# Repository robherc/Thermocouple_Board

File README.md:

# Thermocouple_Board
Ultra-fast, Ultra-Precise Thermocouple reading board with SPI and Analog outputs

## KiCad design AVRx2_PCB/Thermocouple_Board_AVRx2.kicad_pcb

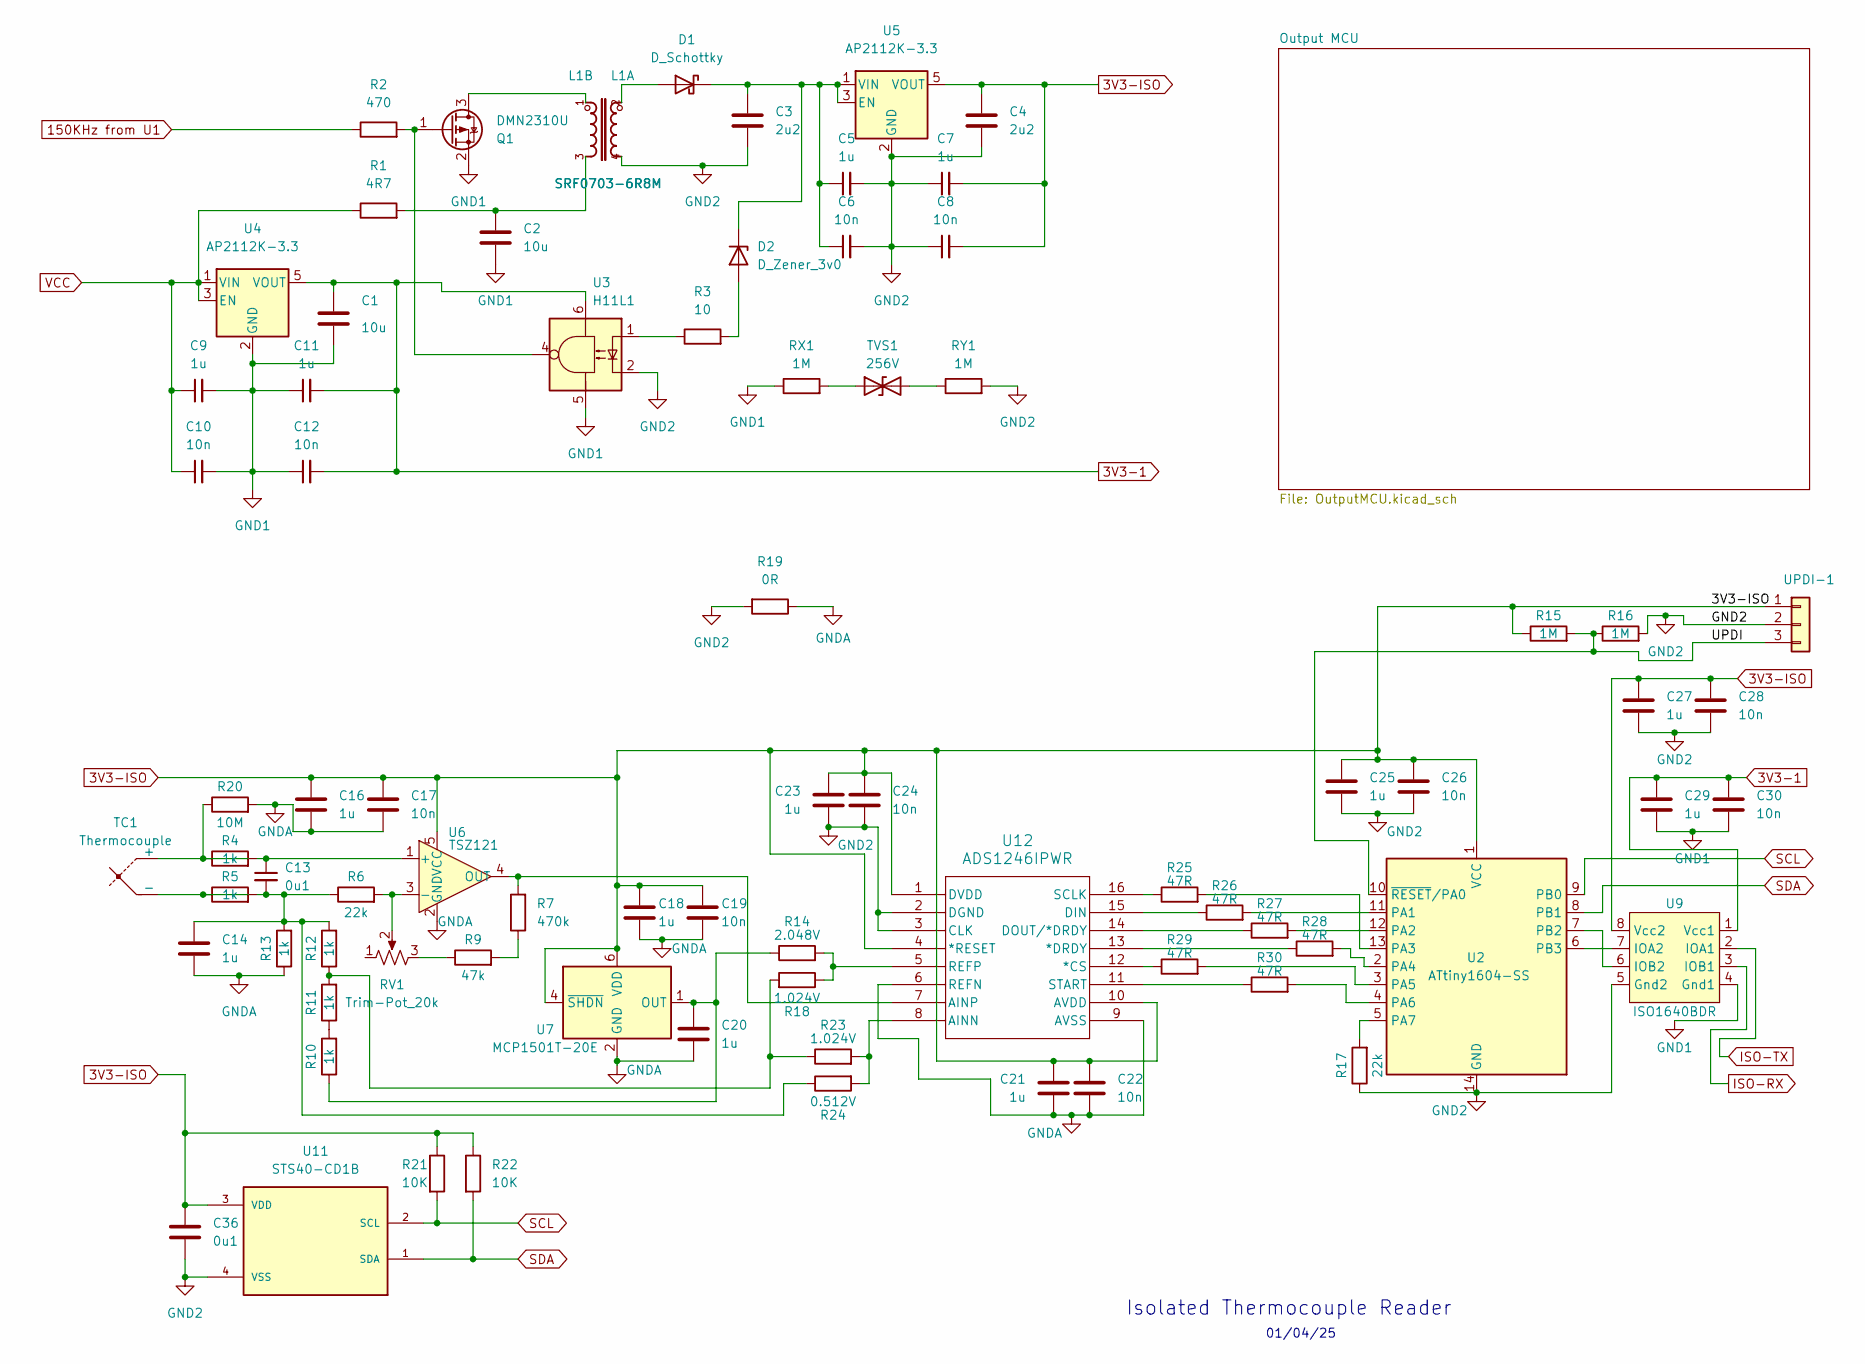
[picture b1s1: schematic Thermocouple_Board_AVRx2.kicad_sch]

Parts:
C1, C2: 10u; C_0805_2012Metric_Pad1.18x1.45mm_HandSolder
C3, C4: 2u2; C_0603_1608Metric
C5, C7, C9, C11, C14, C16, C18, C20, C21, C23, C25, C27, C29: 1u; C_0402_1005Metric
C6, C8, C10, C12, C17, C19, C22, C24, C26, C28, C30: 10n; C_0402_1005Metric
C13, C36: 0u1; C_0402_1005Metric
D1: D_Schottky; D_2010_5025Metric_Pad1.52x2.65mm_HandSolder
D2: D_Zener_3v0; D_SOD-123
J6: UPDI-1; PinHeader_1x03_P2.54mm_Vertical
L1: SRF0703-6R8M; 0703; MPN SRF0703-220M
Q1: DMN2310U; SOT-23
R1: 4R7; R_2512_6332Metric
R2: 470; R_0402_1005Metric
R3: 10; R_1206_3216Metric
R4, R5, R10, R11, R12, R13: 1k; R_0603_1608Metric
R6, R17: 22k; R_0603_1608Metric
R7: 470k; R_0603_1608Metric
R9: 47k; R_0603_1608Metric
R14: 2.048V; R_0402_1005Metric_Pad0.72x0.64mm_HandSolder
R15, R16: 1M; R_0603_1608Metric
R18, R23: 1.024V; R_0402_1005Metric_Pad0.72x0.64mm_HandSolder
R19: 0R; R_1206_3216Metric_Pad1.30x1.75mm_HandSolder
R20: 10M; R_0402_1005Metric
R21, R22: 10K; R_0603_1608Metric
R24: 0.512V; R_0402_1005Metric_Pad0.72x0.64mm_HandSolder
R25, R26, R27, R28, R29, R30: 47R; R_0603_1608Metric
RV1: Trim-Pot_20k; TRIM_TC33X-2-203E
RX1: 1M; R_0603_1608Metric
RY1: 1M; R_0603_1608Metric
TC1: Thermocouple; TypeKSocket
TVS1: 256V; DO-214AA
U2: ATtiny1604-SS; SOIC-14_3.9x8.7mm_P1.27mm
U3: H11L1; H11L1-4
U4, U5: AP2112K-3.3; SOT-23-5
U6: TSZ121; SOT-353_SC-70-5
U7: MCP1501T-20E; SOT-23-6
U9: ISO1640BDR; SOIC-8_3.9x4.9mm_P1.27mm
U11: STS40-CD1B; STS4X
U12: ADS1246IPWR; PW16

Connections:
3V3-1: C1.1, C11.2, C12.2, C29.1, C30.1, U3.6, U4.5 (VOUT), U9.1 (Vcc1); also elsewhere on the board
3V3-ISO: C4.1, C7.2, C8.2, C16.1, C17.1, C18.1, C19.1, C21.1, C22.1, C23.1, C24.1, C25.1, C26.1, C27.1, C28.1, C36.1, J6.1, R15.1, R21.1, R22.1, U2.1 (VCC), U5.5 (VOUT), U6.5 (VCC), U7.4 (~SHDN), U7.6 (VDD), U9.8 (Vcc2), U11.3 (VDD), U12.1 (DVDD), U12.4 (*RESET), U12.10 (AVDD)
150KHz from U1: R2.1; also elsewhere on the board
/UPDI: J6.3, R15.2, R16.1, U2.10 (~RESET/PA0)
GND1: C1.2, C2.2, C9.2, C10.2, C11.1, C12.1, C29.2, C30.2, Q1.2 (S), RX1.1, U3.5, U4.2 (GND), U4.4 (NC), U9.4 (Gnd1); also elsewhere on the board
GND2: C3.2, C4.2, C5.2, C6.2, C7.1, C8.1, C23.2, C24.2, C25.2, C26.2, C27.2, C28.2, C36.2, J6.2, L1.4, R16.2, R17.1, R19.2, RY1.2, U2.14 (GND), U3.2, U3.3, U5.2 (GND), U5.4 (NC), U9.5 (Gnd2), U11.4 (VSS), U12.2 (DGND), U12.3 (CLK)
GNDA: C14.2, C16.2, C17.2, C18.2, C19.2, C20.2, C21.2, C22.2, R13.1, R19.1, R20.2, U6.2 (GND), U7.2 (GND), U7.3 (GND), U7.5 (GND), U12.6 (REFN), U12.9 (AVSS)
ISO-RX: U9.3 (IOB1); also elsewhere on the board
ISO-TX: U9.2 (IOA1); also elsewhere on the board
unnamed: C2.1, L1.3, R1.2
unnamed: C13.2, C14.1, R5.2, R6.1, R12.2, R13.2, R24.1
unnamed: D1.2 (A), L1.2
unnamed: C3.1, C5.1, C6.1, D1.1 (K), D2.1 (K), U5.1 (VIN), U5.3 (EN)
unnamed: D2.2 (A), R3.2
unnamed: L1.1, Q1.3 (D)
unnamed: Q1.1 (G), R2.2, U3.4
unnamed: R3.1, U3.1
unnamed: R7.1, R9.2
unnamed: R9.1, RV1.3
unnamed: R10.2, R11.1
unnamed: R11.2, R12.1, R18.2, R23.1
unnamed: R4.1, R20.1, TC1.1 (+)
unnamed: R5.1, TC1.2 (-)
unnamed: RX1.2, TVS1.1 (A1)
unnamed: RY1.1, TVS1.2 (A2)
unnamed: R26.2, U2.11 (PA1)
unnamed: R27.2, U2.12 (PA2)
unnamed: R25.2, U2.13 (PA3)
unnamed: R28.2, U2.2 (PA4)
unnamed: R29.2, U2.3 (PA5)
unnamed: R30.2, U2.4 (PA6)
unnamed: R17.2, U2.5 (PA7)
unnamed: U2.7 (PB2), U9.6 (IOB2)
unnamed: U2.6 (PB3), U9.7 (IOA2)
unnamed: C13.1, R4.2, U6.1 (+)
unnamed: R6.2, RV1.2, U6.3 (-)
unnamed: C20.1, R10.1, R14.1, U7.1 (OUT)
unnamed: R29.1, U12.12 (*CS)
unnamed: R28.1, U12.13 (*DRDY)
unnamed: R23.2, R24.2, U12.8 (AINN)
unnamed: R7.2, U6.4 (OUT), U12.7 (AINP)
unnamed: R26.1, U12.15 (DIN)
unnamed: R27.1, U12.14 (DOUT/*DRDY)
unnamed: R14.2, R18.1, U12.5 (REFP)
unnamed: R25.1, U12.16 (SCLK)
unnamed: R30.1, U12.11 (START)
SCL: R21.2, U2.9 (PB0), U11.2 (SCL)
SDA: R22.2, U2.8 (PB1), U11.1 (SDA)
VCC: C9.1, C10.1, R1.1, U4.1 (VIN), U4.3 (EN); also elsewhere on the board

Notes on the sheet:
Isolated Thermocouple Reader
01/04/25

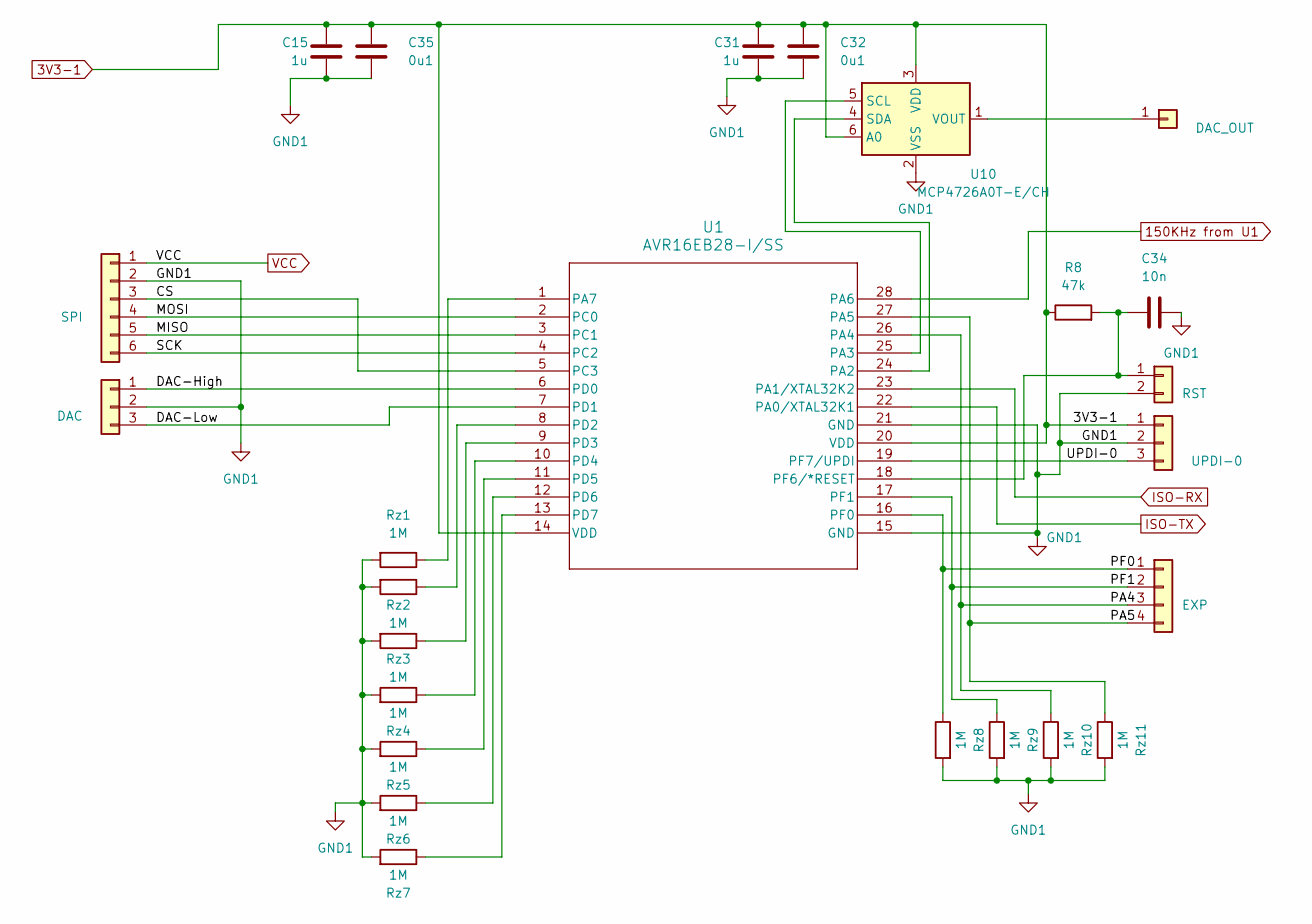
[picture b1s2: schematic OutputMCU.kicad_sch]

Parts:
C15, C31: 1u; C_0402_1005Metric
C32, C35: 0u1; C_0402_1005Metric
C34: 10n; C_0402_1005Metric
J1: DAC_OUT; PinHeader_1x01_P2.54mm_Vertical
J2: SPI; PinHeader_1x06_P2.54mm_Vertical
J3: RST; PinHeader_1x02_P2.54mm_Vertical
J4: DAC; PinHeader_1x03_P2.54mm_Vertical
J5: UPDI-0; PinHeader_1x03_P2.54mm_Vertical
J7: EXP; PinHeader_1x04_P2.54mm_Vertical
R8: 47k; R_0603_1608Metric
Rz1, Rz2, Rz3, Rz4, Rz5, Rz6, Rz7, Rz8, Rz9, Rz10, Rz11: 1M; R_0603_1608Metric
U1: AVR16EB28-I/SS; SSOP28_SS_MCH
U10: MCP4726A0T-E/CH; SOT-23-6

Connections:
3V3-1: C15.1, C31.1, C32.1, C35.1, J5.1, R8.1, U1.14 (VDD), U1.20 (VDD), U10.3 (VDD), U10.6 (A0); also elsewhere on the board
150KHz from U1: U1.28 (PA6); also elsewhere on the board
/Output MCU/CS: J2.3, U1.5 (PC3)
/Output MCU/DAC-High: J4.1, U1.6 (PD0)
/Output MCU/DAC-Low: J4.3, U1.7 (PD1)
/Output MCU/MISO: J2.5, U1.3 (PC1)
/Output MCU/MOSI: J2.4, U1.2 (PC0)
/Output MCU/PA4: J7.3, Rz10.1, U1.26 (PA4)
/Output MCU/PA5: J7.4, Rz11.1, U1.27 (PA5)
/Output MCU/PF0: J7.1, Rz8.1, U1.16 (PF0)
/Output MCU/PF1: J7.2, Rz9.1, U1.17 (PF1)
/Output MCU/SCK: J2.6, U1.4 (PC2)
/Output MCU/UPDI-0: J5.3, U1.19 (PF7/UPDI)
GND1: C15.2, C31.2, C32.2, C34.1, C35.2, J2.2, J3.2, J4.2, J5.2, Rz1.2, Rz2.2, Rz3.2, Rz4.2, Rz5.2, Rz6.2, Rz7.2, Rz8.2, Rz9.2, Rz10.2, Rz11.2, U1.15 (GND), U1.21 (GND), U10.2 (VSS); also elsewhere on the board
ISO-RX: U1.23 (PA1/XTAL32K2); also elsewhere on the board
ISO-TX: U1.22 (PA0/XTAL32K1); also elsewhere on the board
unnamed: J1.1, U10.1 (VOUT)
unnamed: C34.2, J3.1, R8.2, U1.18 (PF6/*RESET)
unnamed: U1.24 (PA2), U10.4 (SDA)
unnamed: U1.25 (PA3), U10.5 (SCL)
unnamed: Rz1.1, U1.1 (PA7)
unnamed: Rz2.1, U1.8 (PD2)
unnamed: Rz3.1, U1.9 (PD3)
unnamed: Rz4.1, U1.10 (PD4)
unnamed: Rz5.1, U1.11 (PD5)
unnamed: Rz6.1, U1.12 (PD6)
unnamed: Rz7.1, U1.13 (PD7)
VCC: J2.1; also elsewhere on the board

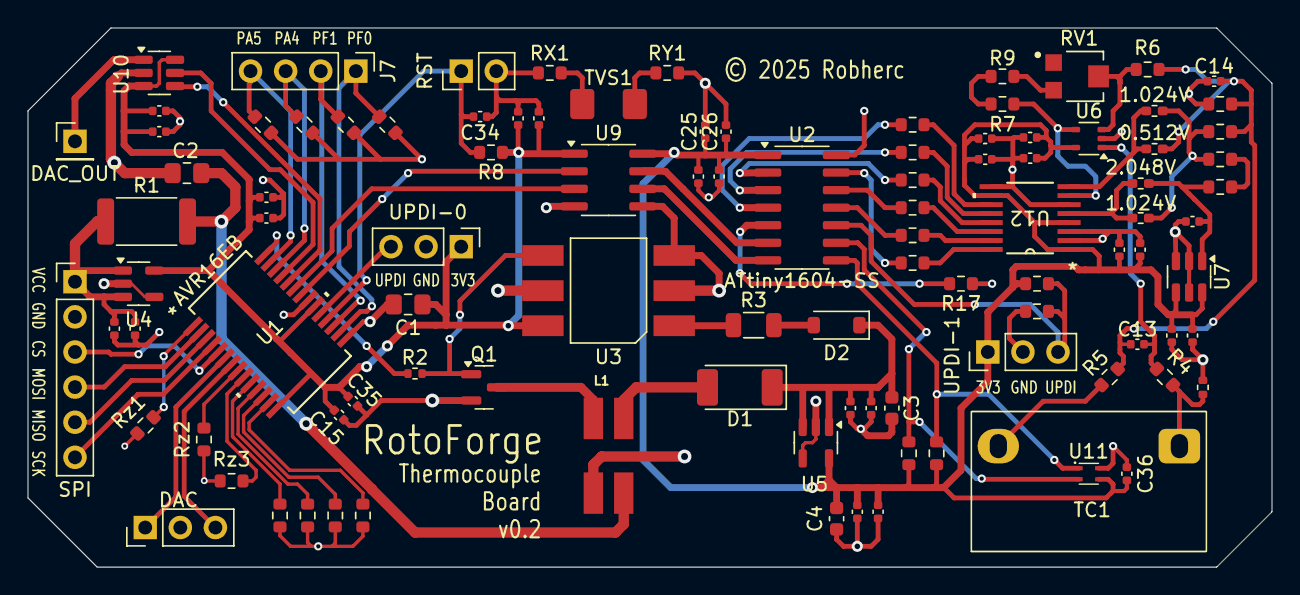
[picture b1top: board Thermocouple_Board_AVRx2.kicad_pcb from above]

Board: 2 copper layers, 90.0 x 39.0 mm, 103 parts (1 on the bottom side), 71 nets.

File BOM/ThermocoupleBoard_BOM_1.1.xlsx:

Source: | /home/robherc/Projects/RotoForge/Isolated Thermocouple Board/ThermocoupleBoard1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
Date: | Fri 17 Jan 2025 01:48:11 AM EST
Tool: | Eeschema 7.0.11+dfsg-1build4
Generator: | /usr/share/kicad/plugins/bom_csv_grouped_by_value_with_fp.py
Component Count: | 85
Ref | Qnty | Value | Cmp name | Footprint | Description | Part # | Vendor | Link
C1, C2 | 2 | 10u | C | Capacitor_SMD:C_0805_2012Metric | Ceramic capacitor | 1276-1096-1-ND | DigiKey | https://www.digikey.com/en/products/detail/samsung-electro-m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
C3, C4 | 2 | 2u2 | C | Capacitor_SMD:C_0603_1608Metric | Ceramic capacitor | 1276-1040-1-ND | DigiKey | https://www.digikey.com/en/products/detail/samsung-electro-m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
C5, C7, C9, C11, C14, C15, C16, C18, C20, C21, C23, C25, C27, C29 | 14 | 1u | C | Capacitor_SMD:C_0402_1005Metric | Ceramic capacitor | 1276-1076-1-ND | DigiKey | https://www.digikey.com/en/products/detail/samsung-electro-m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
C6, C8, C10, C12, C17, C19, C22, C24, C26, C28, C30, C34 | 12 | 10n | C | Capacitor_SMD:C_0402_1005Metric | Ceramic capacitor | 490-1313-1-ND | DigiKey | https://www.digikey.com/en/products/detail/murata-electronic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
C13, C35, C36 | 3 | 0u1 | C | Capacitor_SMD:C_0402_1005Metric | Ceramic capacitor | 490-6328-1-ND | DigiKey | https://www.digikey.com/en/products/detail/murata-electronic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
C33 | 1 | 0.47u | C | Capacitor_SMD:C_0402_1005Metric | Ceramic capacitor | 490-3264-1-ND | DigiKey | https://www.digikey.com/en/products/detail/murata-electronic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
D1 | 1 | D_Schottky | D_Schottky | Diode_SMD:D_2010_5025Metric | Schottky barrier diode | 4878-SK14CT-ND | DigiKey | https://www.digikey.com/en/products/detail/diotec-semiconduc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
D2 | 1 | D_Zener_3v0 | D_Zener | Diode_SMD:D_SOD-123 | Zener diode 3V0 | MMSZ4683-TPMSCT-ND | DigiKey | https://www.digikey.com/en/products/detail/micro-commercial-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
J1 | 1 | DAC_OUT | Conn_01x01 | PinHeader_1x01_P2.54mm_Vertical | Single Header Pin | SAM1112-01-ND | DigiKey | https://www.digikey.com/en/products/detail/samtec-inc/TS-101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
J2 | 1 | SPI | Conn_01x06 | PinHeader_1x06_P2.54mm_Vertical | 2.54mm 6-pin header | SAM1112-06-ND | DigiKey | https://www.digikey.com/en/products/detail/samtec-inc/TS-106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
J3 | 1 | RST | Conn_01x02 | PinHeader_1x02_P2.54mm_Vertical | 2.54mm 2-pin header | SAM1112-02-ND | DigiKey | https://www.digikey.com/en/products/detail/samtec-inc/TS-102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
J4 | 1 | DAC | Conn_01x03 | PinHeader_1x03_P2.54mm_Vertical | 2.54mm 3-pin header | SAM1112-03-ND | DigiKey | https://www.digikey.com/en/products/detail/samtec-inc/TS-103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
J5 | 1 | SWD | Conn_01x04 | PinHeader_1x04_P2.54mm_Vertical | 2.54mm 4-pin header | SAM1112-04-ND | DigiKey | https://www.digikey.com/en/products/detail/samtec-inc/TS-104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
J6 | 1 | UPDI | Conn_01x03 | PinHeader_1x03_P2.54mm_Vertical | 2.54mm 3-pin header | SAM1112-03-ND | DigiKey | https://www.digikey.com/en/products/detail/samtec-inc/TS-103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
L1 | 1 | SRF0703-6R8M | SRF0703-220M | custom:0703 | 6.8uH SMPS dual-coil inductor/xfmr | SRF0703-6R8MCT-ND | DigiKey | https://www.digikey.com/en/products/detail/bourns-inc/SRF070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
Q1 | 1 | DMN2310U | DMG2301L | Package_TO_SOT_SMD:SOT-23 | MOSFET BVDSS: 8V~24V SOT23 | 31-DMN2310U-7CT-ND | DigiKey | https://www.digikey.com/en/products/detail/diodes-incorporat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
R1 | 1 | 4R7 | R | Resistor_SMD:R_2512_6332Metric | Resistor | CR2512-J/-4R7ELF | DigiKey | https://www.digikey.com/en/products/detail/bourns-inc/CR2512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
R2 | 1 | 470R | R | Resistor_SMD:R_0402_1005Metric | Resistor | RC0402FR-07470RL | DigiKey | https://www.digikey.com/en/products/detail/yageo/RC0402FR-07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
R3 | 1 | 10R | R | Resistor_SMD:R_1206_3216Metric | Resistor | WR12X100 JTL | DigiKey | https://www.digikey.com/en/products/detail/walsin-technology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
R4, R5, R10, R11, R12, R13 | 6 | 1k | R | Resistor_SMD:R_0603_1608Metric | Resistor | RC0603DR-071KL | DigiKey | https://www.digikey.com/en/products/detail/yageo/RC0603DR-07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
R6, R14, R17 | 3 | 22k | R | Resistor_SMD:R_0603_1608Metric | Resistor | RT0603DRE0722KL | DigiKey | https://www.digikey.com/en/products/detail/yageo/RT0603DRE07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
R7 | 1 | 470k | R | Resistor_SMD:R_0603_1608Metric | Resistor | RT0603DRE07470KL | DigiKey | https://www.digikey.com/en/products/detail/yageo/RT0603DRE07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
R8, R9 | 2 | 47k | R | Resistor_SMD:R_0603_1608Metric | Resistor | RC0603DR-0747KL | DigiKey | https://www.digikey.com/en/products/detail/yageo/RC0603DR-07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
R15, R16 | 2 | 1M | R | Resistor_SMD:R_0603_1608Metric | Resistor | 560112116074 | DigiKey | https://www.digikey.com/en/products/detail/w%C3%BCrth-elektr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
R19 | 1 | 0R | R | Resistor_SMD:R_1206_3216Metric | Resistor | RMCF1206ZT0R00 | DigiKey | https://www.digikey.com/en/products/detail/stackpole-electro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
R20 | 1 | 10M | R | Resistor_SMD:R_0402_1005Metric | Resistor | AC0402JR-0710ML | DigiKey | https://www.digikey.com/en/products/detail/yageo/AC0402JR-07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
R21, R22 | 2 | 10K | R | Resistor_SMD:R_0603_1608Metric | Resistor | 560112116005 | DigiKey | https://www.digikey.com/en/products/detail/w%C3%BCrth-elektr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
RV1 | 1 | Trim-Pot_20k | R_Potentiometer_US | custom:TRIM_TC33X-2-203E | 20k Trim-Pot | TC33X-2-203ECT-ND | DigiKey | https://www.digikey.com/en/products/detail/bourns-inc/TC33X-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
RX1 | 1 | 1M | R | Resistor_SMD:R_0603_1608Metric | Resistor | 560112116074 | DigiKey | https://www.digikey.com/en/products/detail/w%C3%BCrth-elektr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
RY1 | 1 | 1M | R | Resistor_SMD:R_0603_1608Metric | Resistor | 560112116074 | DigiKey | https://www.digikey.com/en/products/detail/w%C3%BCrth-elektr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
Rz1, Rz2, Rz3 | 3 | 22k | R | Resistor_SMD:R_0603_1608Metric | Resistor | 560112116022 | DigiKey | https://www.digikey.com/en/products/detail/w%C3%BCrth-elektr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
TC1 | 1 | Thermocouple | Thermocouple | custom:TypeKSocket | Thermocouple Socket | PCC-SMP-U | AliExpress | https://www.aliexpress.us/item/3256805330271859.html
TVS1 | 1 | 256V | D_TVS | custom:DO-214AA | Bidirectional TVS diode | 13-P6SMB300CA-AT/TR13CT-ND | DigiKey | https://www.digikey.com/en/products/detail/yageo/P6SMB300CA-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
U1 | 1 | MSPM0G1507SPTR | MSPM0G1507SPTR | Package_QFP:LQFP-48_7x7mm_P0.5mm | 80MHz 32-bit ARM Mixed-Signal MCU | MSPM0G1507SPTR | DigiKey | https://www.digikey.com/en/products/detail/texas-instruments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
U2 | 1 | ATtiny1604-SS | ATtiny1604-SS | Package_SO:SOIC-14_3.9x8.7mm_P1.27mm | AtTiny1604 – 20MHz, SOIC-14 | ATTINY1604-SSNR | DigiKey | https://www.digikey.com/en/products/detail/microchip-technol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
U3 | 1 | H11L1 | H11L1 | custom:H11L1-4 | SMPS control feedback OptoIsolator | H11L1SM | DigiKey | https://www.digikey.com/en/products/detail/isocom-components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
U4, U5 | 2 | AP2112K-3.3 | AP2112K-3.3 | Package_TO_SOT_SMD:SOT-23-5 | 600mA LDO, 3.8V-6V in, 3.3V out | AP2112K-3.3TRG1 | DigiKey | https://www.digikey.com/en/products/detail/diodes-incorporat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
U6 | 1 | TSZ121 | TSZ121ICT | Package_TO_SOT_SMD:SOT-353_SC-70-5 | IC OPAMP ZERO DRIFT | TSZ121ICT | DigiKey | https://www.digikey.com/en/products/detail/stmicroelectronic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
U7 | 1 | MCP1501T-20E | MCP1501-10xCH | Package_TO_SOT_SMD:SOT-23-6 | 2.048V, 0.1%, 20mA, Precision Vref | MCP1501T-20E/CHY | DigiKey | https://www.digikey.com/en/products/detail/microchip-technol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
U8 | 1 | MCP3565R | MCP3565R | custom:MCP3565 | SPI ADC 24-bit | MCP3565RT-E/SFX | DigiKey | https://www.digikey.com/en/products/detail/microchip-technol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
U9 | 1 | ISO1640BDR | ISO6721RB | Package_SO:SOIC-8_3.9x4.9mm_P1.27mm | Bi-Directional Digital Isolator, 1.7MHz | ISO1640BDR | DigiKey | https://www.digikey.com/en/products/detail/texas-instruments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
U11 | 1 | STS40-CD1B | STS4X | custom:STS4X | I2C Temperature Sensor | STS40-CD1B-R3 | DigiKey | https://www.digikey.com/en/products/detail/sensirion-ag/STS4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
JP1 | 2 | Shorting Jumper | Shorting Jumper | N/A | 2.54mm Header-pins Jumper | QPC02SXGN-RC | DigiKey | https://www.digikey.com/en/products/detail/sullins-connector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

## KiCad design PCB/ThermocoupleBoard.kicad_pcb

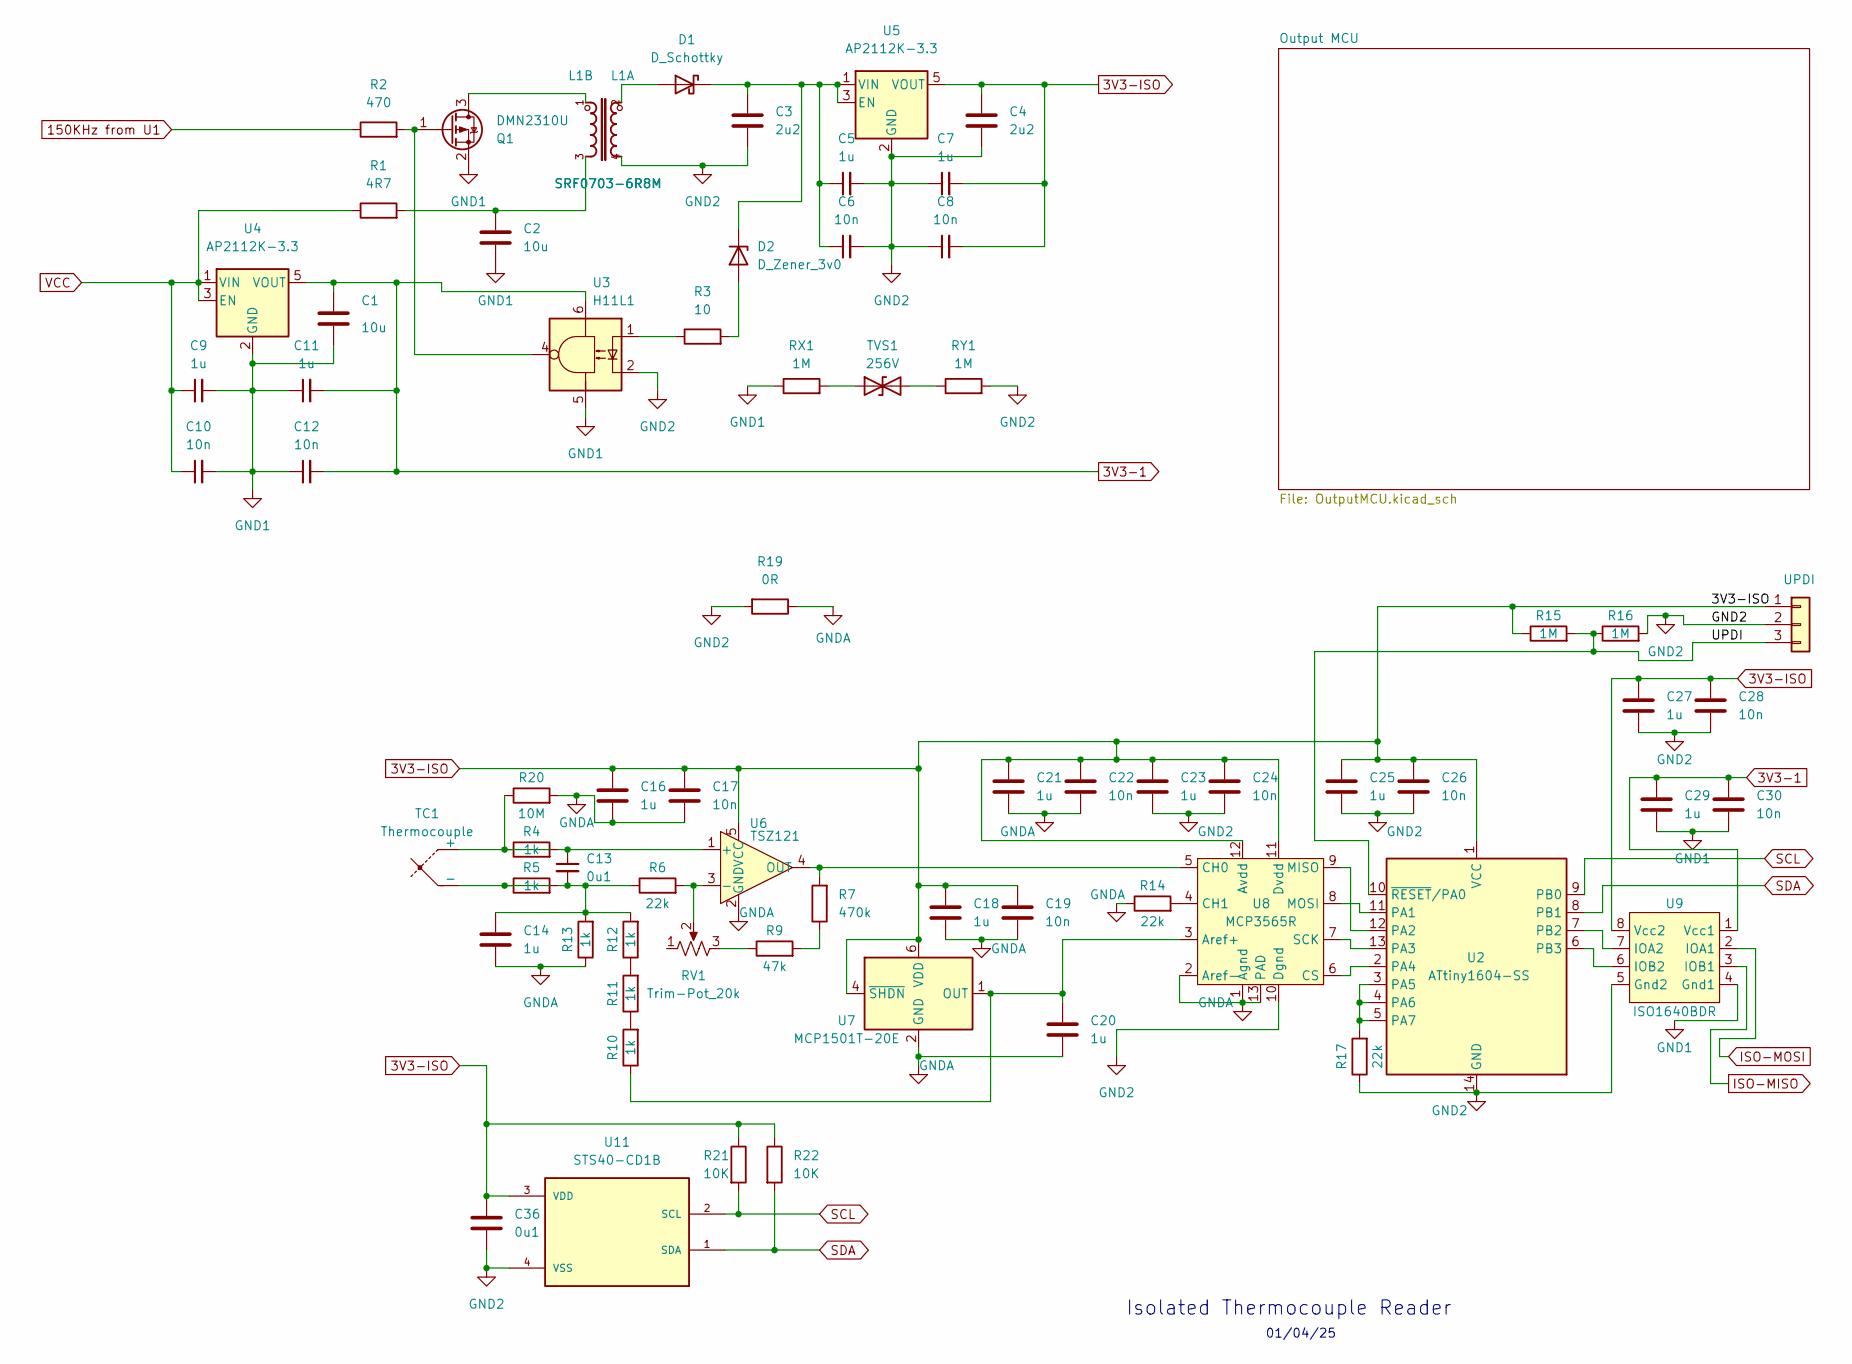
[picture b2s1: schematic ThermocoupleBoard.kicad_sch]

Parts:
C1, C2: 10u; C_0805_2012Metric_Pad1.18x1.45mm_HandSolder
C3, C4: 2u2; C_0603_1608Metric
C5, C7, C9, C11, C14, C16, C18, C20, C21, C23, C25, C27, C29: 1u; C_0402_1005Metric
C6, C8, C10, C12, C17, C19, C22, C24, C26, C28, C30: 10n; C_0402_1005Metric
C13, C36: 0u1; C_0402_1005Metric
D1: D_Schottky; D_2010_5025Metric_Pad1.52x2.65mm_HandSolder
D2: D_Zener_3v0; D_SOD-123
J6: UPDI; PinHeader_1x03_P2.54mm_Vertical
L1: SRF0703-6R8M; 0703; MPN SRF0703-220M
Q1: DMN2310U; SOT-23
R1: 4R7; R_2512_6332Metric
R2: 470; R_0402_1005Metric
R3: 10; R_1206_3216Metric
R4, R5, R10, R11, R12, R13: 1k; R_0603_1608Metric
R6, R14, R17: 22k; R_0603_1608Metric
R7: 470k; R_0603_1608Metric
R9: 47k; R_0603_1608Metric
R15, R16: 1M; R_0603_1608Metric
R19: 0R; R_1206_3216Metric_Pad1.30x1.75mm_HandSolder
R20: 10M; R_0402_1005Metric
R21, R22: 10K; R_0603_1608Metric
RV1: Trim-Pot_20k; TRIM_TC33X-2-203E
RX1: 1M; R_0603_1608Metric
RY1: 1M; R_0603_1608Metric
TC1: Thermocouple; TypeKSocket
TVS1: 256V; DO-214AA
U2: ATtiny1604-SS; SOIC-14_3.9x8.7mm_P1.27mm
U3: H11L1; H11L1-4
U4, U5: AP2112K-3.3; SOT-23-5
U6: TSZ121; SOT-353_SC-70-5
U7: MCP1501T-20E; SOT-23-6
U8: MCP3565R; MCP3565
U9: ISO1640BDR; SOIC-8_3.9x4.9mm_P1.27mm
U11: STS40-CD1B; STS4X

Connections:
3V3-1: C1.1, C11.2, C12.2, C29.1, C30.1, U3.6, U4.5 (VOUT), U9.1 (Vcc1); also elsewhere on the board
3V3-ISO: C4.1, C7.2, C8.2, C16.1, C17.1, C18.1, C19.1, C21.1, C22.1, C23.1, C24.1, C25.1, C26.1, C27.1, C28.1, C36.1, J6.1, R15.1, R21.1, R22.1, U2.1 (VCC), U5.5 (VOUT), U6.5 (VCC), U7.4 (~SHDN), U7.6 (VDD), U8.11 (Dvdd), U8.12 (Avdd), U9.8 (Vcc2), U11.3 (VDD)
150KHz from U1: R2.1; also elsewhere on the board
/UPDI: J6.3, R15.2, R16.1, U2.10 (~RESET/PA0)
GND1: C1.2, C2.2, C9.2, C10.2, C11.1, C12.1, C29.2, C30.2, Q1.2 (S), RX1.1, U3.5, U4.2 (GND), U4.4 (NC), U9.4 (Gnd1); also elsewhere on the board
GND2: C3.2, C4.2, C5.2, C6.2, C7.1, C8.1, C23.2, C24.2, C25.2, C26.2, C27.2, C28.2, C36.2, J6.2, L1.4, R16.2, R17.1, R19.2, RY1.2, U2.14 (GND), U3.2, U3.3, U5.2 (GND), U5.4 (NC), U8.10 (Dgnd), U9.5 (Gnd2), U11.4 (VSS)
GNDA: C14.2, C16.2, C17.2, C18.2, C19.2, C20.2, C21.2, C22.2, R13.1, R14.1, R19.1, R20.2, U6.2 (GND), U7.2 (GND), U7.3 (GND), U7.5 (GND), U8.1 (Agnd), U8.2 (Aref-), U8.13 (PAD)
ISO-MISO: U9.3 (IOB1); also elsewhere on the board
ISO-MOSI: U9.2 (IOA1); also elsewhere on the board
unnamed: C2.1, L1.3, R1.2
unnamed: C13.2, C14.1, R5.2, R6.1, R12.2, R13.2
unnamed: D1.2 (A), L1.2
unnamed: C3.1, C5.1, C6.1, D1.1 (K), D2.1 (K), U5.1 (VIN), U5.3 (EN)
unnamed: D2.2 (A), R3.2
unnamed: L1.1, Q1.3 (D)
unnamed: Q1.1 (G), R2.2, U3.4
unnamed: R3.1, U3.1
unnamed: R7.1, R9.2
unnamed: R9.1, RV1.3
unnamed: R10.2, R11.1
unnamed: R11.2, R12.1
unnamed: R4.1, R20.1, TC1.1 (+)
unnamed: R5.1, TC1.2 (-)
unnamed: RX1.2, TVS1.1 (A1)
unnamed: RY1.1, TVS1.2 (A2)
unnamed: U2.11 (PA1), U8.8 (MOSI)
unnamed: U2.12 (PA2), U8.9 (MISO)
unnamed: U2.13 (PA3), U8.7 (SCK)
unnamed: U2.2 (PA4), U8.6 (CS)
unnamed: R17.2, U2.3 (PA5), U2.4 (PA6), U2.5 (PA7)
unnamed: U2.7 (PB2), U9.7 (IOA2)
unnamed: U2.6 (PB3), U9.6 (IOB2)
unnamed: C13.1, R4.2, U6.1 (+)
unnamed: R6.2, RV1.2, U6.3 (-)
unnamed: R7.2, U6.4 (OUT), U8.5 (CH0)
unnamed: C20.1, R10.1, U7.1 (OUT), U8.3 (Aref+)
unnamed: R14.2, U8.4 (CH1)
SCL: R21.2, U2.9 (PB0), U11.2 (SCL)
SDA: R22.2, U2.8 (PB1), U11.1 (SDA)
VCC: C9.1, C10.1, R1.1, U4.1 (VIN), U4.3 (EN); also elsewhere on the board

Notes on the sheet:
Isolated Thermocouple Reader
01/04/25

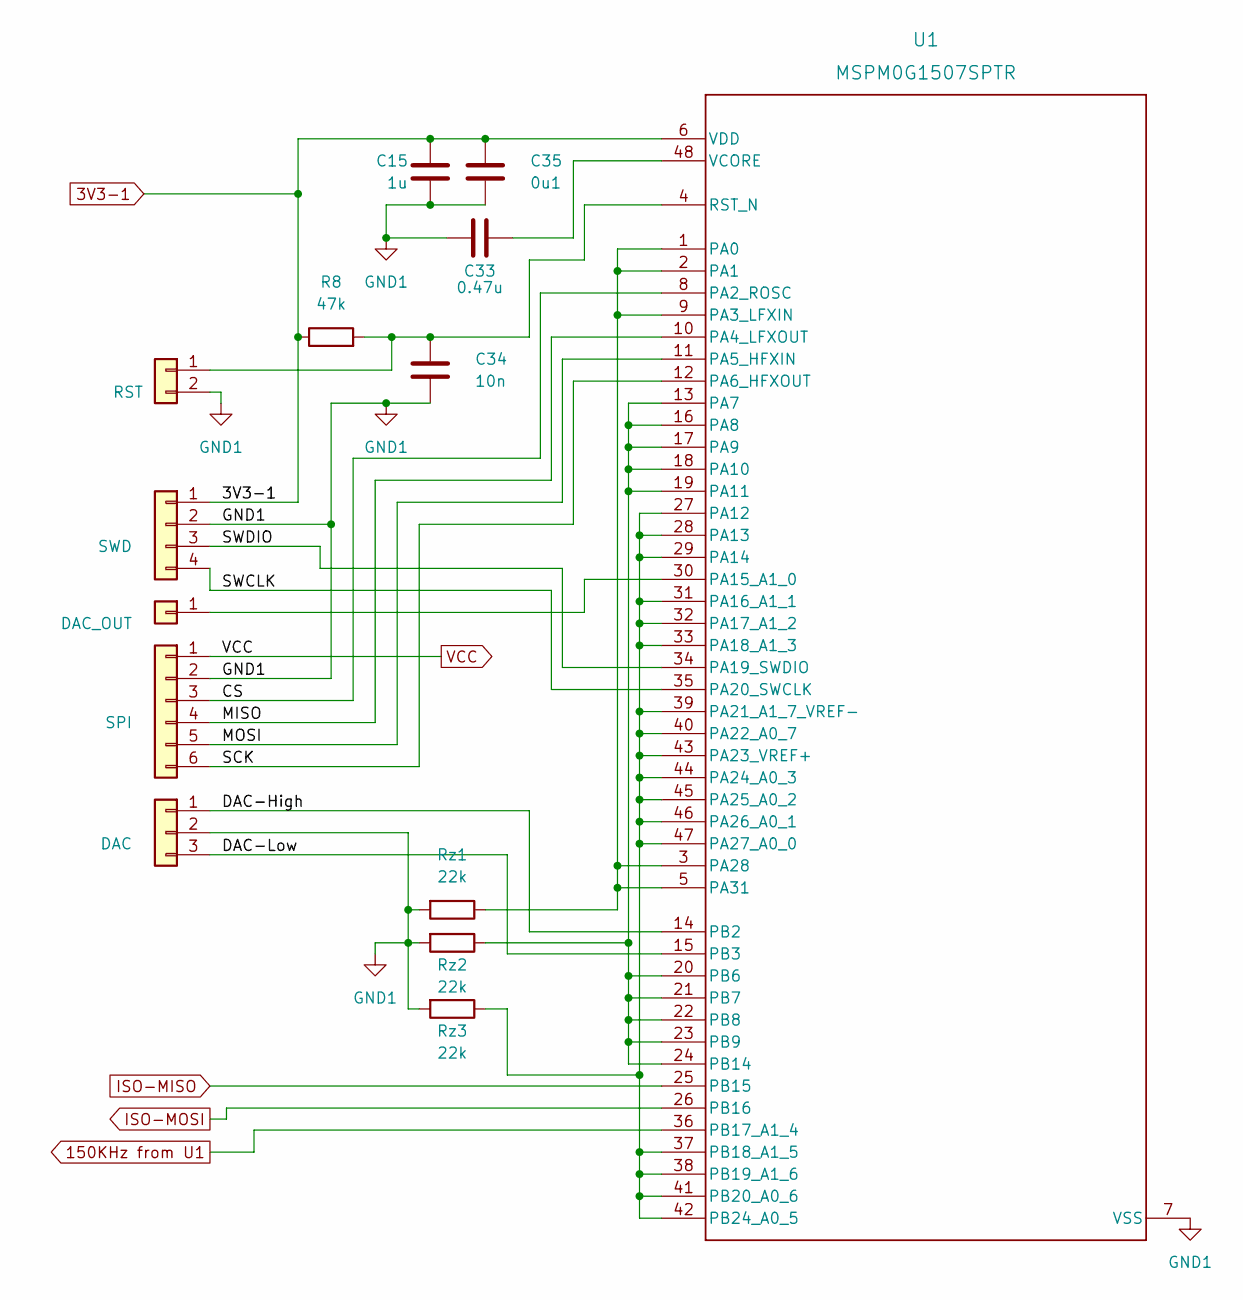
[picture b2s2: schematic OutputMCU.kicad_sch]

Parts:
C15: 1u; C_0402_1005Metric
C33: 0.47u; C_0402_1005Metric
C34: 10n; C_0402_1005Metric
C35: 0u1; C_0402_1005Metric
J1: DAC_OUT; PinHeader_1x01_P2.54mm_Vertical
J2: SPI; PinHeader_1x06_P2.54mm_Vertical
J3: RST; PinHeader_1x02_P2.54mm_Vertical
J4: DAC; PinHeader_1x03_P2.54mm_Vertical
J5: SWD; PinHeader_1x04_P2.54mm_Vertical
R8: 47k; R_0603_1608Metric
Rz1, Rz2, Rz3: 22k; R_0603_1608Metric
U1: MSPM0G1507SPTR; LQFP-48_7x7mm_P0.5mm

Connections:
3V3-1: C15.1, C35.1, J5.1, R8.1, U1.6 (VDD); also elsewhere on the board
150KHz from U1: U1.36 (PB17_A1_4); also elsewhere on the board
/Output MCU/CS: J2.3, U1.8 (PA2_ROSC)
/Output MCU/DAC-High: J4.1, U1.14 (PB2)
/Output MCU/DAC-Low: J4.3, U1.15 (PB3)
/Output MCU/MISO: J2.4, U1.10 (PA4_LFXOUT)
/Output MCU/MOSI: J2.5, U1.11 (PA5_HFXIN)
/Output MCU/SCK: J2.6, U1.12 (PA6_HFXOUT)
/Output MCU/SWCLK: J5.4, U1.35 (PA20_SWCLK)
/Output MCU/SWDIO: J5.3, U1.34 (PA19_SWDIO)
GND1: C15.2, C33.2, C34.2, C35.2, J2.2, J3.2, J4.2, J5.2, Rz1.2, Rz2.2, Rz3.2, U1.7 (VSS); also elsewhere on the board
ISO-MISO: U1.25 (PB15); also elsewhere on the board
ISO-MOSI: U1.26 (PB16); also elsewhere on the board
unnamed: J1.1, U1.30 (PA15_A1_0)
unnamed: C34.1, J3.1, R8.2, U1.4 (RST_N)
unnamed: Rz1.1, U1.1 (PA0), U1.2 (PA1), U1.3 (PA28), U1.5 (PA31), U1.9 (PA3_LFXIN)
unnamed: Rz2.1, U1.13 (PA7), U1.16 (PA8), U1.17 (PA9), U1.18 (PA10), U1.19 (PA11), U1.20 (PB6), U1.21 (PB7), U1.22 (PB8), U1.23 (PB9), U1.24 (PB14)
unnamed: Rz3.1, U1.27 (PA12), U1.28 (PA13), U1.29 (PA14), U1.31 (PA16_A1_1), U1.32 (PA17_A1_2), U1.33 (PA18_A1_3), U1.37 (PB18_A1_5), U1.38 (PB19_A1_6), U1.39 (PA21_A1_7_VREF-), U1.40 (PA22_A0_7), U1.41 (PB20_A0_6), U1.42 (PB24_A0_5), U1.43 (PA23_VREF+), U1.44 (PA24_A0_3), U1.45 (PA25_A0_2), U1.46 (PA26_A0_1), U1.47 (PA27_A0_0)
unnamed: C33.1, U1.48 (VCORE)
VCC: J2.1; also elsewhere on the board

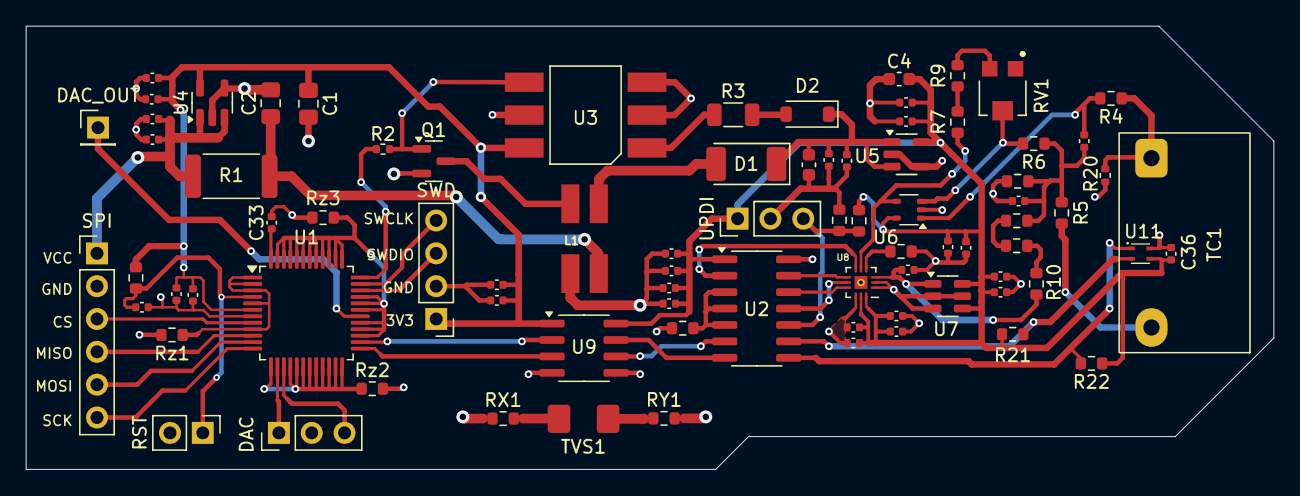
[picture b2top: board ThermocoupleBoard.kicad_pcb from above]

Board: 2 copper layers, 96.5 x 34.3 mm, 83 parts (1 on the bottom side), 54 nets.

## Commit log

2025-01-19 Original Commit
2025-01-20 Added datasheets for most ICs
2025-03-02 Added board prototype v0.2 featuring 2 AVR MCUs
2025-03-02 Fix Typo
2025-03-04 Update pcb designs to further optimize layout, fix an error, and creat prototype layout with test points
2025-03-18 Add ASM test code for first-test on the avr16eb28 chip
2025-03-18 Fixed the ASM code for the first program, now builds, flashes & runs successfully
2025-03-18 Added a second test program to mirror UART to MISO+MOSI for step 2 testing, added a reference & added some code organization
2025-03-19 Add test3 code & update defs
2025-03-19 update smps clock timing for more efficient operation
2025-03-19 removed extraneous files
2025-03-19 Fix a couple of switched traces
2025-03-19 add combined SMPS & UART transparent passthrough test code
2025-03-20 Added datasheets for new parts
2025-03-20 Fix crossed traces that were found during prototype testing
2025-03-20 First test code for the ATTiny 1604
2025-03-20 correction
2025-03-20 Add example terminal commands to build with the gcc14.2+ AVR toolchain
2025-03-21 Add testing code for the 24-bit ADC
2025-03-21 New ADC-only testing code
2025-03-21 Fixed issues with example ADC code
2025-03-31 update to latest kicad version
2025-04-01 Remove files from obsolete RevA, in preparation for RevC progress.
2025-04-01 garbage collection
2025-04-01 Test
2025-04-22 New component datasheet

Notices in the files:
AVRx2_PCB/Thermocouple_Board_AVRx2.kicad_pcb:
© 2025 Robherc
